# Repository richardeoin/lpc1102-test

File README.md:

## LPC1102 test

WLCSP16 and 0201 packages yay

### [parts list](hardware/Parts.md)

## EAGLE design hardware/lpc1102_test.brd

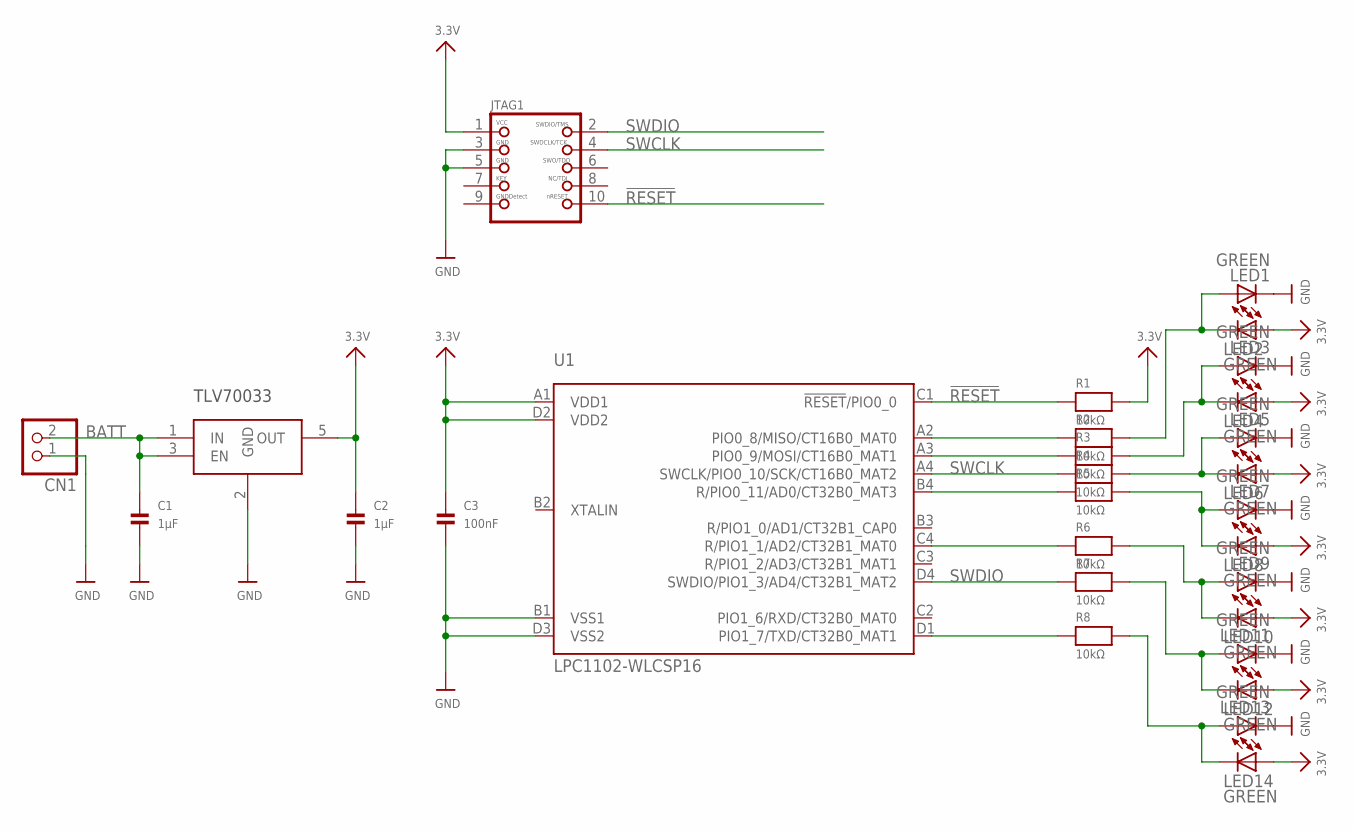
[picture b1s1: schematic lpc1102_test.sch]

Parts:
C1, C2: 1µF; _0402
C3: 100nF; _0402
CN1: JST_2PIN; JSTPH2
JTAG1: JTAG-CORTEXM3SMT; 2X05_1.27MM_SMT
LED1, LED2, LED3, LED4, LED5, LED6, LED7, LED8, LED9, LED10, LED11, LED12, LED13, LED14: GREEN; CHIPLED_0603
R1, R2, R3, R4, R5, R6, R7, R8: 10kΩ; _0201
U1: LPC1102-WLCSP16; WLCSP16
U2: TLV70033DCK; SC70-5L

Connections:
3.3V: C2.1, C3.1, JTAG1.1, LED2.A, LED4.A, LED6.A, LED8.A, LED10.A, LED12.A, LED14.A, R1.2, U1.A1 (VDD1), U1.D2 (VDD2), U2.5 (OUT)
!RESET: JTAG1.10, R1.1, U1.C1 (!RESET!/PIO0_0)
BATT: C1.1, CN1.2, U2.1 (IN), U2.3 (EN)
GND: C1.2, C2.2, C3.2, CN1.1, JTAG1.3, JTAG1.5, LED1.C, LED3.C, LED5.C, LED7.C, LED9.C, LED11.C, LED13.C, U1.B1 (VSS1), U1.D3 (VSS2), U2.2 (GND)
unnamed: R8.1, U1.D1 (PIO1_7/TXD/CT32B0_MAT1)
unnamed: LED1.A, LED2.C, R2.2
unnamed: R6.1, U1.C4 (R/PIO1_1/AD2/CT32B1_MAT0)
unnamed: R5.1, U1.B4 (R/PIO0_11/AD0/CT32B0_MAT3)
unnamed: R3.1, U1.A3 (PIO0_9/MOSI/CT16B0_MAT1)
unnamed: R2.1, U1.A2 (PIO0_8/MISO/CT16B0_MAT0)
unnamed: LED3.A, LED4.C, R3.2
unnamed: LED5.A, LED6.C, R4.2
unnamed: LED7.A, LED8.C, R5.2
unnamed: LED9.A, LED10.C, R6.2
unnamed: LED11.A, LED12.C, R7.2
unnamed: LED13.A, LED14.C, R8.2
SWCLK: JTAG1.4, R4.1, U1.A4 (SWCLK/PIO0_10/SCK/CT16B0_MAT2)
SWDIO: JTAG1.2, R7.1, U1.D4 (SWDIO/PIO1_3/AD4/CT32B1_MAT2)

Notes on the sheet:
TLV70033

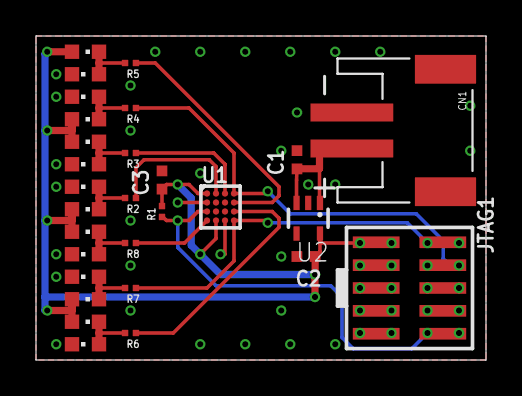
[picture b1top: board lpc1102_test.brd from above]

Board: 2 copper layers, 25.0 x 18.0 mm, 29 parts (0 on the bottom side), 18 nets.

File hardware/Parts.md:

# Parts List

| Part | Description | Supplier | Quantity Required | Notes
| ---  | ---         | ---       | ---               | ---
|LPC1102UK,118|NXP - MCU, 32BIT, CORTEX-M0, 50MHZ, WLCSP-16|[2094271](http://uk.farnell.com/webapp/wcs/stores/servlet/Search?st=2094271)|1|U1 LPC1102UK,118
|20021121-00010C4LF.|FCI - Board-To-Board Connector, Minitek127 20021121 Series, Surface Mount, Header, 10, 1.27 mm, Gold|[1865279](http://uk.farnell.com/webapp/wcs/stores/servlet/Search?st=1865279)|1|JTAG1 arm swd connector 1.27mm
|TLV70033DCKT|TEXAS INSTRUMENTS - IC, LDO, 200MA, 3.3V, 5SC70|[1815750](http://uk.farnell.com/webapp/wcs/stores/servlet/Search?st=1815750)|1|U2 200mA 3.3v ldo
|ERJ1GNF1002C|PANASONIC ELECTRONIC COMPONENTS - Surface Mount Chip Resistor, Thick Film, AEC-Q200 ERJ Series, 10 kohm, 50 mW, Â± 1%, 25 V|[2302362](http://uk.farnell.com/webapp/wcs/stores/servlet/Search?st=2302362)|8|R1, R2, R3, R4, R5, R6, R7, R8 10kΩ
|KPT-1608SGC|KINGBRIGHT - LED, GREEN, 12MCD, 568NM, 0603|[2099223](http://uk.farnell.com/webapp/wcs/stores/servlet/Search?st=2099223)|14|LED1-LED14 green led
|MC0603X105K100CT|MULTICOMP - SMD Multilayer Ceramic Capacitor, MC Series, 1 ÂµF, Â± 10%, X5R, 10 V, 0603 [1608 Metric]|[1759399](http://uk.farnell.com/webapp/wcs/stores/servlet/Search?st=1759399)|2|C1, C2 1µF
|MC0603B104K500CT|MULTICOMP - SMD Multilayer Ceramic Capacitor, MC Series, 0.1 ÂµF, Â± 10%, X7R, 50 V, 0603 [1608 Metric]|[1759122](http://uk.farnell.com/webapp/wcs/stores/servlet/Search?st=1759122)|1|C3 100nF

## Useful items

| Part | Description | Supplier | Quantity Required | Notes
| ---  | ---         | ---       | ---               | ---
|FFSD-05-D-06.00-01-N|SAMTEC - RIBBON CABLE, IDC, 152.4MM, GREY, 10WAY|[1667659](http://uk.farnell.com/webapp/wcs/stores/servlet/Search?st=1667659)|0|10way 1.27mm

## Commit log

2015-09-21 lpc1102 test hardware feat 0201

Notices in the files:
parts and their libraries:
microbuilder_v2: This work is placed in the public domain, and may be freely used for commercial and non-commercial work with the following conditions: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
